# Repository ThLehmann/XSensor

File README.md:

# XSensor

Multi Telemetriesensor für Jeti, auf Basis von Arduino

#### Highlights
- alle Sensoren im Code vorhanden und durch Jetibox aktivier und konfigurierbar
- einfachen "in den Code nehmen" durch Änderung eines einzelnen Defines (def.h)
- Leiterkarte zum einfachen Anschluss der Sensoren
- Leiterkarte MUL-6S zum Anschluss eines 6S Akkus mit Einzelzellenüberwachung

#### Sensoren
- Drehzahl
- Durchfluss, Benzin/Kerosin
- Temperatur 4x NTC / 7x IR
- Höhe
- Vario
- Pitot Rohr, Geschwindigkeit
- GPS NEMA Format
- PWM Messung
- 6x Spannung
- 3x MUI (Strom, Leistung, Kapazität)
- G-Force, vorbereitet

#### Hardware
- Motherboard: Arudino Mini Pro 5V, CPU 328P
- Drehzahl   : Hallsensor zB TLE4905L, Conrad Bestellnr: 153751-62
- Durchfluss : Turbine: BioTech FCH-m-POM-LC / Durchflussmenge 50mL - 3000mL
- Durchfluss : Benzin : BioTech FCH-m-PP-LC / Durchflussmenge 15mL - 800mL
- Temperatur : NTC MF58 3950 5K 5% / Tempbereich -45° bis 300°
- Temperatur : MLX90614 per I2C, Infrarot / Berührungslos
- Drucksensor: MS5611
- Pitot Rohr : MPXV7002DP siehe RC-Thought
- GPS        : NEO 6M
- Strom      : diverse ACSxx, siehe Code oder JetiBox
- MUL6S      : Einzelzellenspannung
- PWM        : PWM Impulsmessung
- G-Force    : ADXL345, not implemented yet

#### PCB
- Adapterboard für steckbare Sensoren, unterstützt drei verschiedene Pro Mini Boards
 - unten mit 5 Pinnen
 - unten mit 3 Pinnen, rechts 2 Pinne
 - unten keine Pinne, rechts 2x2 Pinne 
- MUL-6S für Akku Einzelzellenüberwachung

#### Software
- Bootloader Optiboot bringt 1,5kB zusätzlichen Speicherplatz
- Arduino IDE Version 1.8.9

#### besondere Konfigurationseigenschaften
- Sensor Nr., sollten mehrere XSensor in einem Modell eingesetzt werden
- Watchdog, Überwachung der ordnungsgemäßen Funktion des Sensors (!! prüfen ob Bootloader das ordnungsgemäß unterstützt)
- Referenzspannung für ADC Mesuungen (Spg/Strom), wichtig um genaue Messergebnisse zu erhalten. Mit Multimeter die Vcc Spg. messen
- Kalibrierung des Stromsensors, im Ruhebetrieb sollte kein Strom fliessen
- Rücksetzen aller Werte auf Auslieferzustand !!! vorher überlegen ob sinnvoll !!!
- Debug, Anzeige des verbleibenden Speichers, dieser sollte größer 100 Byte sein, ansonsten droht Fehlfunktion

#### Konfigurationskonzept
Änderungen werden NICHT direkt gespeichert, erst nachdem wieder ganz nach oben (Pfeil hoch) gegangen ist erfolgt eine Abfrage ob die Änderungene gespeichert oder verworfen werden sollen.
Mit Taste rechts links wird zwichen den Hauptmenues gewechselt, mit Taste runter in das entsprechend ausgeählte.
Um etwas zu aktivieren ist Taste links und rechts gleichzeitig zu betätigen. Leider werden Tastendrücke vom Sender nicht immer korrekt übermittelt, dies ist zu beachten. Mit etwas Gewöhnung sieht man aber schnell ob das Gewünschte ausgeführt wurde.

#### LED Anzeige
Der Sensor Status wird mit vier unterschiedlichen Blinkrhytmen angezeigt.
LED ein / aus
- 100mS / 1500mS Ruhebetrieb
- 1400mS / 200mS kein Sensor aktiv
- 100mS / 100mS Sensor Initialisierungs Fehler
- 800mS / 800mS Sensor Fehler während Betrieb

Eine Anzeige beim entspr. Sensor erfolgt in der Jetibox um zu ermitteln welcher Sensor betroffen ist
- I = Init
- F = Laufzeit

#### Compilieren
Sollte der Codespeicher nicht reichen, weil zB ein anderer Bootloader als Optiboot eingesetzt wird, können nicht gewünschte Eigenschaften ausgeblendet werden. In der def.h sind entsprechende defines zu finden (_SENS_XX_). Den entsprechenden Sensor einfach durch '1' einblenden oder '0' ausblenden.
Die fest zugeordneten Ports sind ab Zeile 160 zu sehen.

# Sensoren

### Drehzahl (1x)
- Anzahl Magnete / Auslösungen je Umdrehung
- Genauigkeit / Abrunden des Drehzahlwertes
- Anzeige der Auslösungen auf JB zum Sensor Test

Sensorwerte:
- aktuelle  Drehzahl
- Anzahl Umdrehungen gesamt
- Betriebszeit

### Durchfluss (1x)
- Tankvolumen
- Rücksetzen
-- automatisch nach jedem Sensor Neustart (typ. Turbine)
-- manuell per Taster (typ. Schleppmodell)
- Anzahl Impulse je Liter
-- manuell änderbar
-- Kalibrierbar
- Anzeige der Auslösungen auf JB zum Sensor Test

Sensorwerte:
- verbleibende Tankmenge in mL
- verbrauchte Menge in mL
- akt. Durchfluss in ml/Min
- gesamt verbrauchte Menge

### Temperatur (4xNTC / 7x IR)
- NTC (Wärmewiderstand) an Analogport
- IR (Infrarot) per I2C

Sensorwerte:
- Temperatur 1-7

### Höhe / Vario (1x)
- Vario Sensibilität (Filter) und Totzone

Sensorwerte:
- relative Höhe bezogen auf Starthöhe
- gesamt Höhe, Summe aller gemachten Höhenmeter
- Temperatur
- Vario

### GPS (1x)

Sensorwerte:
- Anzahl aktiver Satelliten
- Position, Längen und Breitengrad
- relative Höhe bezogen auf Starthöhe
- Geschwindigkeit
- max. Geschwindigkeit
- akt. Kurs / Richtung in Grad 0-359
- Richtung in Grad zum Modell, gemessen vom Startpunkt
- Enfernung zum Modell, gemessen vom Startpunkt
- zurückgelegte Strecke, Trip und gesamt

### Pitot Rohr (1x)

Sensorwerte:
- Geschwindigkeit

### Spannung / MUL (6x)
- analog Port
- Widerstand gegen GND
- Widerstand gegen Vcc

Sensorwerte:
- Spannung

### Spannung-Strom-Leistung / MUI (3x)
- diverse ACS konfigurierbar, uni als auch bidirektionale Typen
- Kalibrierbar
- Rückstellen der verbrauchten Kapazität
-- automatisch nach jedem Sensor Neustart
-- automatisch bei n% höherer Akkuspannung nach neustart (Akku geladen)
-- manuell durch Taster oder Jetibox
- analog Port
- Widerstand gegen GND
- Widerstand gegen Vcc

Sensorwerte:
- Strom
- Spannung
- Leistung
- entnommene Kapazität

### PWM Messung (1x)
Sensorwerte:
- Impulsdauer eines PWM Signals

### Jetibox
Summenwerte sind per Jetibox rücksetzbar
- Anzahl Umdrehungen
- Motor Betriebszeit
- Tankvolumen
- gesamt Durchfluss
- entnommene Akku Kapazität
- max. Geschwindigkeit
- gesamt zurückgelegte Strecke

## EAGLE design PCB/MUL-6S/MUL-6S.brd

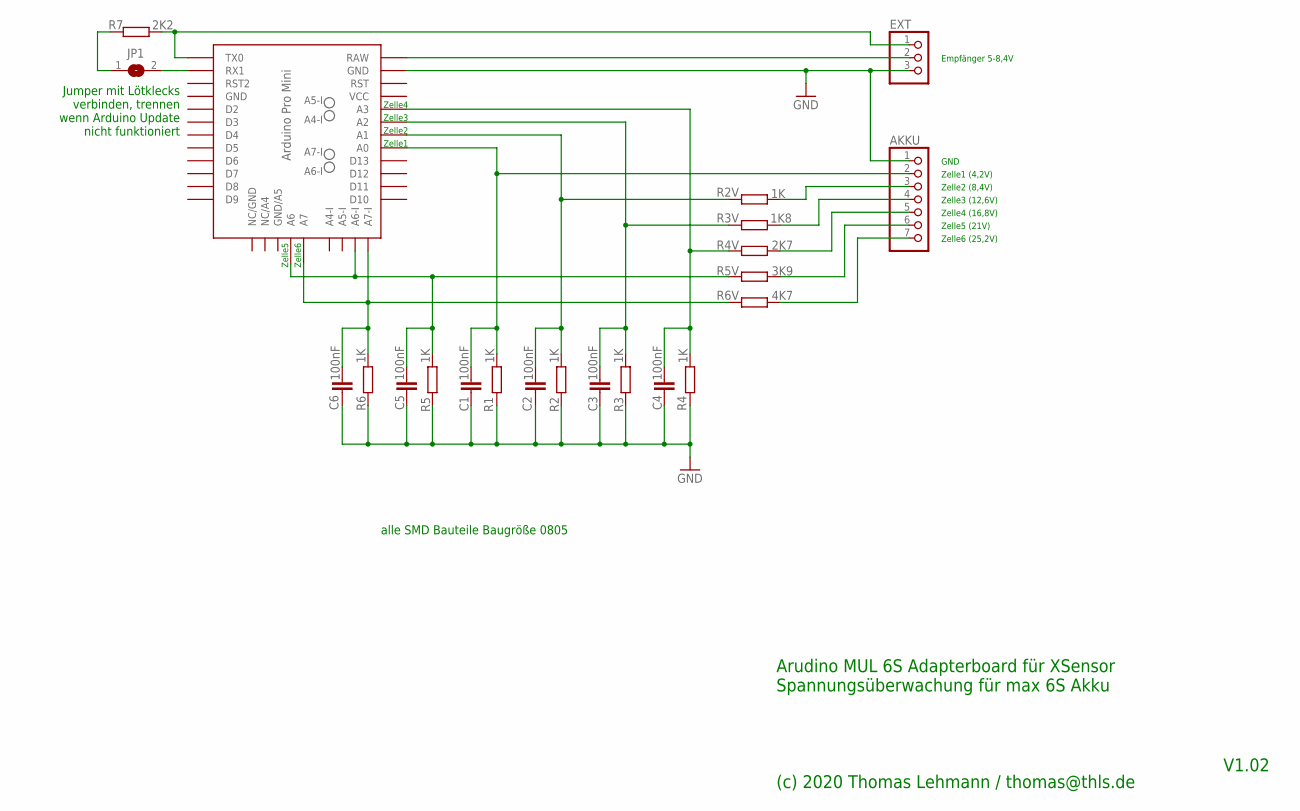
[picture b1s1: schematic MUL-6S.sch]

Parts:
AKKU: 1X07/90
C1, C2, C3, C4, C5, C6: 100nF; C0805K
EXT: 1X03/90
JP1: SJ
R1, R2, R2V, R3, R4, R5, R6: 1K; R0805
R3V: 1K8; R0805
R4V: 2K7; R0805
R5V: 3K9; R0805
R6V: 4K7; R0805
R7: 2K2; R0805
U$1: PRO-MINI-5PIN-KLPAD

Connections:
GND: AKKU.1, C1.2, C2.2, C3.2, C4.2, C5.2, C6.2, EXT.3, R1.2, R2.2, R3.2, R4.2, R5.2, R6.2, U$1.GND, U$1.GND1 (GND)
unnamed: C4.1, R4.1, R4V.1, U$1.A3
unnamed: EXT.2, U$1.RAW
unnamed: EXT.1, R7.2, U$1.TX0
unnamed: JP1.1, R7.1
unnamed: AKKU.3, R2V.2
unnamed: AKKU.4, R3V.2
unnamed: AKKU.5, R4V.2
unnamed: AKKU.6, R5V.2
unnamed: AKKU.7, R6V.2
unnamed: AKKU.2, C1.1, R1.1, U$1.A0
unnamed: C5.1, R5.1, R5V.1, U$1.A6, U$1.A6-I
unnamed: C6.1, R6.1, R6V.1, U$1.A7, U$1.A7-I
unnamed: JP1.2, U$1.RX1
unnamed: C2.1, R2.1, R2V.1, U$1.A1
unnamed: C3.1, R3.1, R3V.1, U$1.A2

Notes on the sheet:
Zelle1
Zelle2
Zelle3
Zelle4
Zelle5
Zelle6
Zelle1 (4,2V)
Zelle2 (8,4V)
Zelle3 (12,6V)
Zelle4 (16,8V)
Zelle5 (21V)
Zelle6 (25,2V)
GND
Empfänger 5-8,4V
Arudino MUL 6S Adapterboard für XSensor Spannungsüberwachung für max 6S Akku
(c) 2020 Thomas Lehmann / thomas@thls.de
V1.02
Jumper mit Lötklecks verbinden, trennen wenn Arduino Update nicht funktioniert
alle SMD Bauteile Baugröße 0805

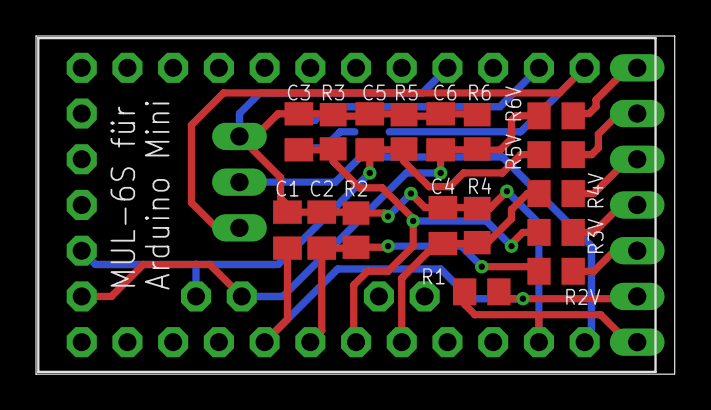
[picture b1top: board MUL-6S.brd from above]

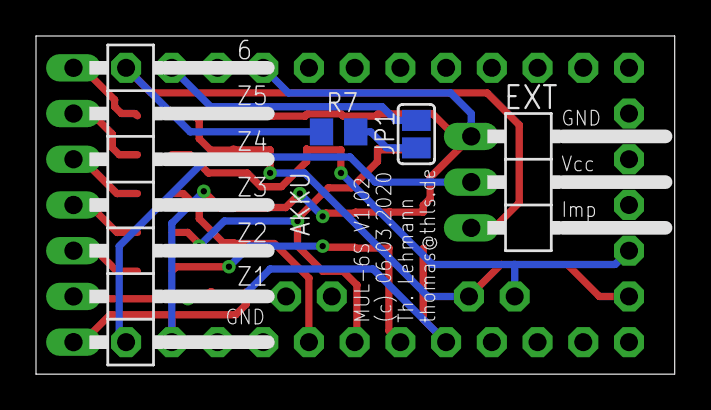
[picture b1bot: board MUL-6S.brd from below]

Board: 2 copper layers, 35.5 x 18.8 mm, 22 parts (2 on the bottom side), 16 nets.

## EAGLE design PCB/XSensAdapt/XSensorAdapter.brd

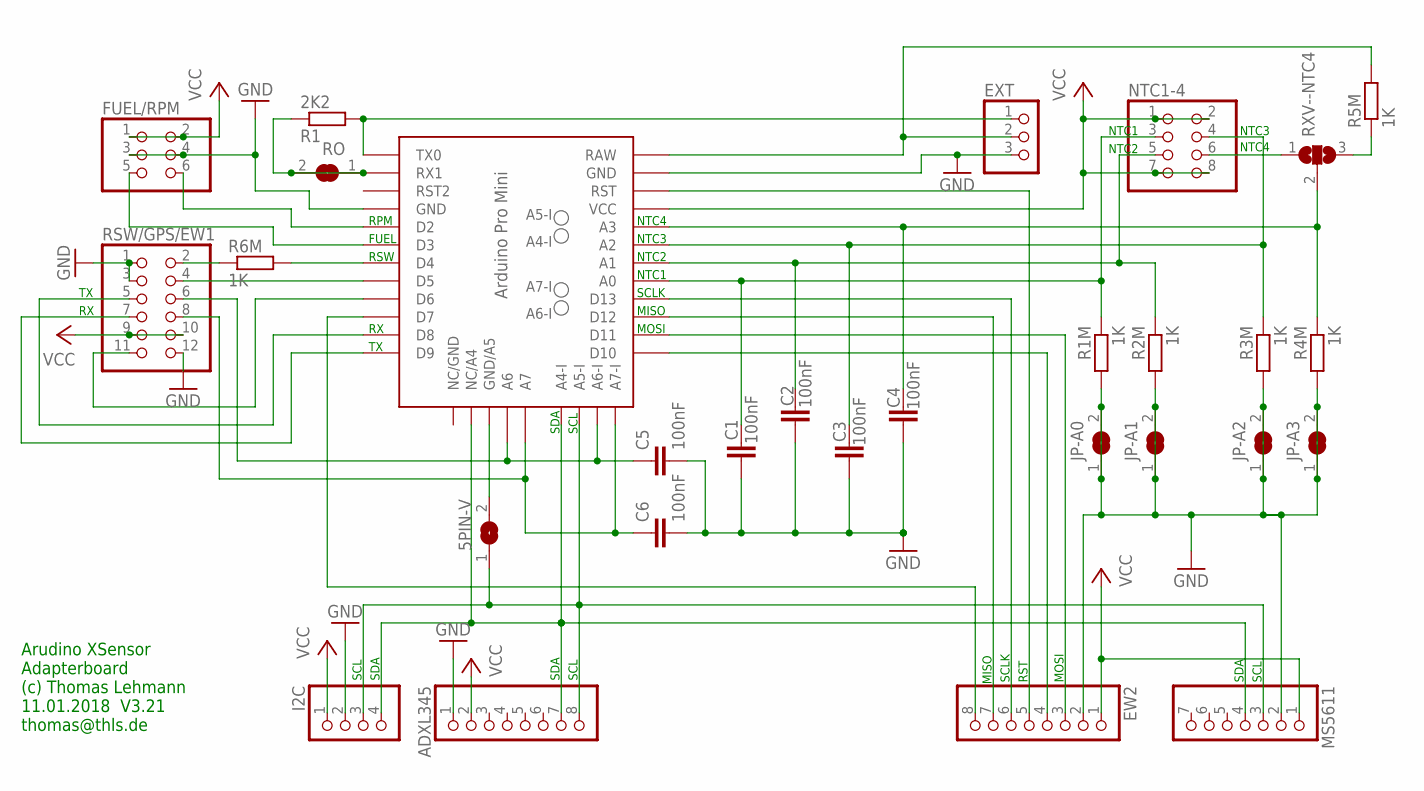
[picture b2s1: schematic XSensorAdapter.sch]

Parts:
5PIN-V: SJ
ADXL345: 1X08
C1, C2, C3, C4, C5, C6: 100nF; C2.5-2
EW2: 1X08
EXT: 1X03
FUEL/RPM: 2X03
I2C: 1X04
JP-A0, JP-A1, JP-A2, JP-A3: SJ
MS5611: 1X07
NTC1-4: 2X04
R1: 2K2; 0207/10
R1M, R2M, R3M, R4M, R5M, R6M: 1K; 0207/10
RO: SJ
RSW/GPS/EW1: 2X06
RXV--NTC4: SJ_2
U$1: PRO-MINI-5PINPRO-MINI-5PIN; PRO-MINI-5PIN

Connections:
GND: ADXL345.1, C1.2, C2.2, C3.2, C4.2, C5.2, C6.2, EW2.2, EXT.3, FUEL/RPM.3, FUEL/RPM.4, I2C.2, JP-A0.1, JP-A0.2, JP-A1.1, JP-A1.2, JP-A2.1, JP-A2.2, JP-A3.1, JP-A3.2, MS5611.2, R1M.2, R2M.2, R3M.2, R4M.2, RSW/GPS/EW1.1, RSW/GPS/EW1.3, RSW/GPS/EW1.12, U$1.GND, U$1.GND1 (GND)
unnamed: C4.1, R4M.1, RXV--NTC4.2, U$1.A3
unnamed: EXT.1, R1.2, U$1.TX0
unnamed: RSW/GPS/EW1.7, U$1.D9
unnamed: R5M.1, RXV--NTC4.3
unnamed: C5.1, RSW/GPS/EW1.6, U$1.A6, U$1.A6-I
unnamed: RSW/GPS/EW1.4, U$1.D5
unnamed: RSW/GPS/EW1.5, U$1.D8
unnamed: 5PIN-V.2, U$1.GND/A5
unnamed: C1.1, NTC1-4.3, R1M.1, U$1.A0
unnamed: FUEL/RPM.6, U$1.D2
unnamed: R6M.2, U$1.D4
unnamed: ADXL345.7, I2C.4, MS5611.4, U$1.A4-I, U$1.NC/A4
unnamed: FUEL/RPM.5, U$1.D3
unnamed: R6M.1, RSW/GPS/EW1.2
unnamed: C6.1, RSW/GPS/EW1.8, U$1.A7, U$1.A7-I
unnamed: C2.1, NTC1-4.5, R2M.1, U$1.A1
unnamed: C3.1, NTC1-4.4, R3M.1, U$1.A2
unnamed: EW2.6, U$1.D13
unnamed: EW2.7, U$1.D12
unnamed: EW2.3, U$1.D11
unnamed: EW2.4, U$1.D10
unnamed: EXT.2, R5M.2, U$1.RAW
unnamed: RSW/GPS/EW1.11, U$1.D6
unnamed: NTC1-4.6, RXV--NTC4.1
unnamed: EW2.5, U$1.RST
unnamed: EW2.8, U$1.D7
unnamed: 5PIN-V.1, ADXL345.8, I2C.3, MS5611.3, U$1.A5-I
unnamed: R1.1, RO.1, RO.2, U$1.RX1
VCC: ADXL345.2, EW2.1, FUEL/RPM.1, FUEL/RPM.2, I2C.1, MS5611.1, NTC1-4.1, NTC1-4.2, NTC1-4.7, NTC1-4.8, RSW/GPS/EW1.9, RSW/GPS/EW1.10, U$1.VCC

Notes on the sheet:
Arudino XSensor Adapterboard (c) Thomas Lehmann 11.01.2018 V3.21 thomas@thls.de
SDA
SCL
MOSI
MISO
SCLK
NTC1
NTC2
NTC3
NTC4
RPM
FUEL
RSW
RST

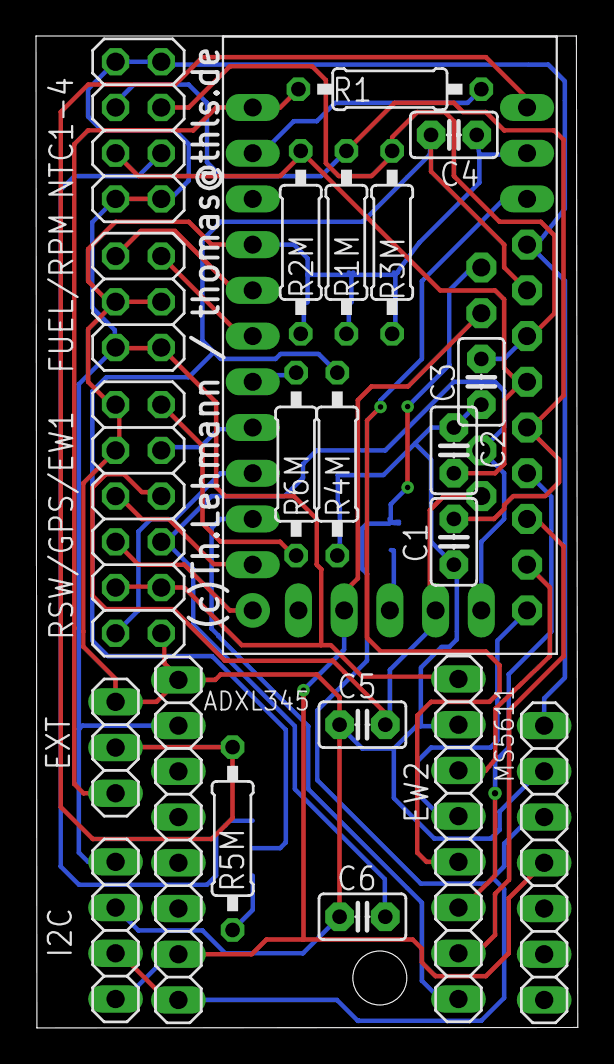
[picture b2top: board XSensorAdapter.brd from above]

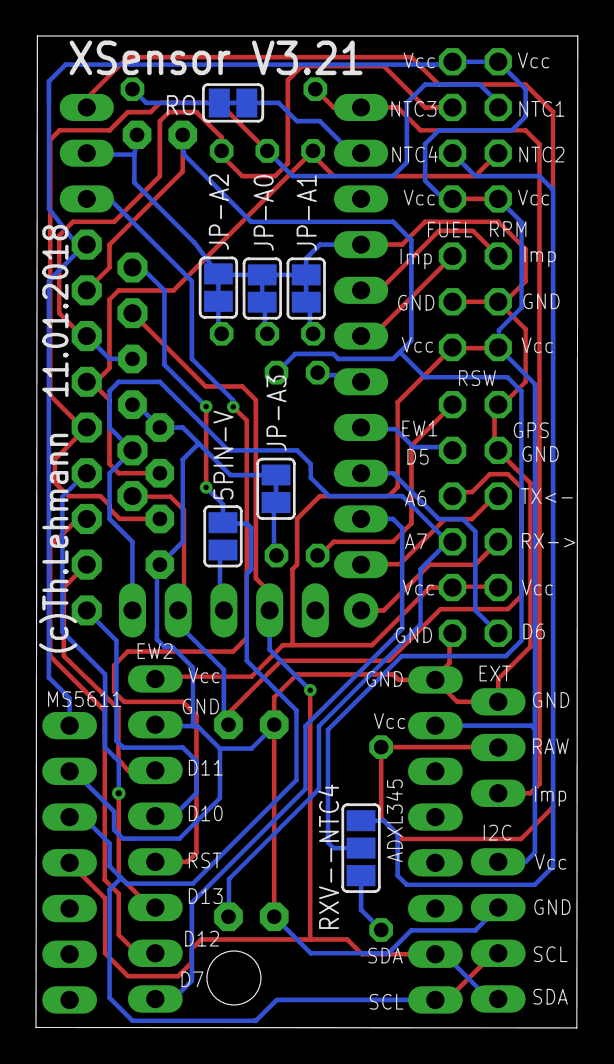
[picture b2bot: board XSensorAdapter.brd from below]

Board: 2 copper layers, 30.1 x 55.1 mm, 29 parts (7 on the bottom side), 30 nets.

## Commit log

2020-01-29 intial commit
2020-01-29 Readme ergänzt Src in XSensor geändet, Arduino IDE verlangt Namen
2020-01-29 readme erweitert
2020-01-29 Unterstrich
2020-01-29 Anpassungen
2020-01-29 ÜSchrift Sensoren
2020-01-29 3. Boardvariante (Bild) ergänzt
2020-02-16 Doku ergänzt
2020-02-16 hinzugefügt
2020-02-25 V2_0_2 MUL-6S PCB
2020-03-09 Zelle 1 war falsch angeschlossen
2020-11-12 Anleitung V2.0.4
